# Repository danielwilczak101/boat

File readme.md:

# Project Boat

IMAGE HERE

Welcome to project boat. Check out our [wiki](https://danielwilczak101.github.io/boat/) for more information.

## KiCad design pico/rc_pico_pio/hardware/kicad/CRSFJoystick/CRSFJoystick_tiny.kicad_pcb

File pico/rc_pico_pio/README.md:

#All of the RoboBoat RC Controls code is build on top of the packages below. 

Would like to give them the credit they deserve.
-Dylan

# ELRSJoystick / CRSFJoystick

<https://github.com/mikeneiderhauser/CRSFJoystick>

Named CRSFJoystick as it indicates the wire protocol between the microcontroller (pi pico) and receiver).

Arduino code using the mbed core that runs on a Pi Pico (2040) to emulate a USB HID Joystick

Pirmarily developed to use and ExpressLRS receiver and a HID Joystick for Sim use! It will work with both Tracer and Crossfire as well.

Shout out to CapnBry for the Crsf Library

https://github.com/CapnBry/CRServoF

Shout out to RealRobots.net for the Gamepad Library

https://gitlab.com/realrobots/PicoGamepad/-/tree/master

# Demo Video

- Blank carrier boards for Pi Pico, Tiny 2040, and Waveshare RP2040 (old stock)
- Built and flashed units
- [DIY Section](#diy-hardware)

A few boards that I believe are based off of this project:
- HGLRC Dongle (I have samples from HGLRC on the way)
  - [HGLRC Dongle at HGLRC](https://www.hglrc.com/collections/new-arrivals/products/hglrc-c1-remote-control)
  - [HGLRC C1 Radio Kit with dongle at HGLRC](https://www.hglrc.com/collections/new-arrivals/products/hglrc-c1-remote-control)
  - [HGLRC C1 Radio Kit with dongle at RacedayQuads](https://www.racedayquads.com/products/hglrc-c1-transmitter-elrs-2-4ghz-choose-your-version?keyword=hglrc%20c1)
- Squid Stick (I have personally not tested one)
  -  [Squid Stick at Progressiverc.com](https://www.progressiverc.com/products/squid-stick-elrs-2-4ghz-usb-receiver-module)
  -  Squid Stick at RacedayQuads - Link to be posted when available
- YMZFPV Simulator Adapter (have not yet been able to confirm that this is based off of this project)
  - [YMZFPV Sim Adapter at RacedayQuads](https://www.racedayquads.com/products/ymzfpv-wireless-simulator-adapter-for-sbus-pwm-csfr-choose-your-version?keyword=simulator)

## Compatability

This project was designed primarily with ELRS usage in mind, however this code base has also been tested with TBS Crossfire Receivers (915MHZ) (last tested v6.16) and TBS Tracer Receivers (2.4GHz) (last tested v6.17) and both appear to work! Flight was teseted in the Liftoff simulator.

I no longer have TBS Crossfire nor TBS Tracer TX modules or Receivers so future tests will have to be conducted by others.

### ExpressLRS (Waveshare RP2040)

### Crossfire

### Tracer

# Building / Flashing

I recently converted the projet to PlatformIO to aid in building, board management, etc.  PlatformIO has some known quirks with PiPico boards and I'm going to leave some breadcrumbs here for later.

## VSCode with PlatformIO

### Installing VSCode and PlatformIO
<https://platformio.org/install/ide?install=vscode>

### Build for specific board / environment

At the Bottom of VSCode you will see a tool bar.  Look for `Default (CRSFJoystick)`.  Building in this state will build for all boards / environments defined in the `platformio.ini` file.  To target a sepecific board, Click on `Default (CRSFJoystick)` and select an appropriate option (Note, selection pops up at the top of vscode).

Click on the Checkmark on the bottom toolbar to build for the board / environment you selected.

Click on the `->` on the bottom toolbar to upload to the board.  If upload fails to find your board, please see bothe the [alternative upload](#alternative-upload) section as well as the driver section.

## Alternative upload
This is one of the standard advertised methods for uploading firmware to a pipico based microcontroller board.

Press and hold the bootsel button on your board and either plugin/power on the board or if the board is already powered press and release the reset button.

This will put the board in RP2 Boot mode.

A removable device should pop up or become available on your computer.  Drag and drop the `firmware.u2f` file from the `.pio/build/wavesharerp2040zero/` directory into this device on your computer.  Note replpace wavesharerp2040zero with the environment for your board.

## Drivers
Drivers can be hit or miss for the pipico board and platformio.  

You may need to use zadig to get vscode+platforio to be able to upload directly to the board.
<https://github.com/platformio/platform-raspberrypi/issues/2#issuecomment-828586398>

Below are the drivers I have working on my Windows 11 machine.  You may need to modify the driver selection via zadig and or device manager to get it working.

- Standard Running Mode
  - RaspberryPi Pico (Interface 0)
    - Zadig -> HidUsb v10.0.22621.819
    - Device Manager -> Human Interface Devices -> HID-compliant game controller
  - RaspberryPi Pico (Interface 1)
      - Zadig -> usbser v10.0.22621.1778
      - Device Manager -> Ports (COM & LPT) -> USB Serial Device
- RP2 Boot mode
  - RP2 Boot (Interface 0) 
    - Zadig USBSTOR v10.0.022621.1778 
    - Device Manager -> Disk Drives -> RPI RP2 USB Device 
  - RP2 Boot (Interface 1)
    - Zadig WinUSB v6.1.7600.16385
    Device Manager -> Universal Serial Bus Devices -> RP2 Boot

### Device manager clicks to change driver 
Right Click -> Properties -> Update Driver -> Browse my computer for drivers -> Let me pick from a list of available drivers on my computer

# Flashing ELRS Receiver

Depending on the device you are using, your target may be different.  For all of the DIY version's I've made, I used the HappyModel EP2 Rx.  Other vendors may vary.

## Flashing via Betaflight Passthrough
<https://www.expresslrs.org/software/updating/betaflight-passthrough/>

## Flashing via Wifi
If your receiver is wifi enabled you can also flash it via wifi

<https://www.expresslrs.org/software/updating/wifi-updating/>

# Testing
For a quick test of functionality, I typically go to [GamepadTester](https://hardwaretester.com/gamepad).

Once the Radio is bound to the RX, it should show up in GamePadTester.

# Mappings
This was a quick map and is not fully featured.

On link up/down the onboard Pi Pico LED will light indicating connection

*NOTE* Channel 5, 6, 7, and 8 are mapped both to analog axis as well as joystick buttons.

| Channel     | Logical Mapping  | Joystick Mapping |
| ----------- | ---------------- | ---------------- |
| 1           | A                | X                |
| 2           | E                | Y                |
| 3           | T                | Rx               |
| 4           | R                | Ry               |
| 5           | Channel 5 (Full) AND AUX1 (1510-2011) | Z  AND Button 0 |
| 6           | Channel 6 (Full) AND AUX2 (1510-2011) | Rz AND Button 1 |
| 7           | Channel 7 (Full) AND AUX3 (1510-2011) | S0 AND Button 2 |
| 8           | Channel 8 (Full) AND AUX4 (1510-2001) | S1 AND Button 3 |
| 9           | AUX5 (1510-2011) | Button 4         |
| 10          | AUX6 (1510-2011) | Button 5         |
| 11          | AUX7 (1510-2011) | Button 6         |
| 12          | AUX8 (1510-2011) | Button 7         |
| 13          | Not Used         | Not Used         |
| 14          | Not Used         | Not Used         |
| 15          | LQ - Not Used    | Not Used         |
| 16          | RSSI - Not Used  | Not Used         |

*Note additional button mappings can be created in caliration.h*

# Here below is for DIY Builds and may be slightly outdated
# DIY Hardware

In a nutshell, wire the ELRS RX up to a uart on the pipico, 5v, and gnd.

| Raspberry Pico | ELRS/CRSF Receiver |
| -------------- | ------------------ |
| VBUS (PIN 40)  | 5V                 |
| GND  (PIN 38)  | GND
| GP4  (PIN 6)   | RX                 |
| GP5  (PIN 7)   | TX                 |

Other boards are supported, see the [board_defs.h](./include/board_defs.h) file.

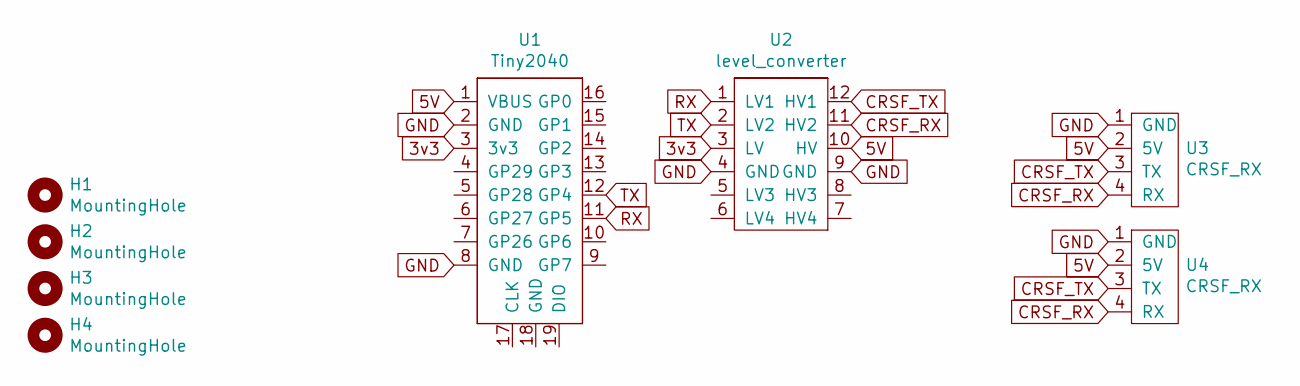
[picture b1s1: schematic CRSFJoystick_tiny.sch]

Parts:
H1, H2, H3, H4: MountingHole; MountingHole_2.2mm_M2
U1: Tiny2040; tiny2040_no_swd
U2: level_converter
U3, U4: CRSF_RX; ELRS_EP2

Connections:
3v3: U1.3 (3v3), U2.3 (LV)
5V: U1.1 (VBUS), U2.10 (HV), U3.2 (5V), U4.2 (5V)
CRSF_RX: U2.11 (HV2), U3.4 (RX), U4.4 (RX)
CRSF_TX: U2.12 (HV1), U3.3 (TX), U4.3 (TX)
GND: U1.2 (GND), U1.8 (GND), U2.4 (GND), U2.9 (GND), U3.1 (GND), U4.1 (GND)
RX: U1.11 (GP5), U2.1 (LV1)
TX: U1.12 (GP4), U2.2 (LV2)

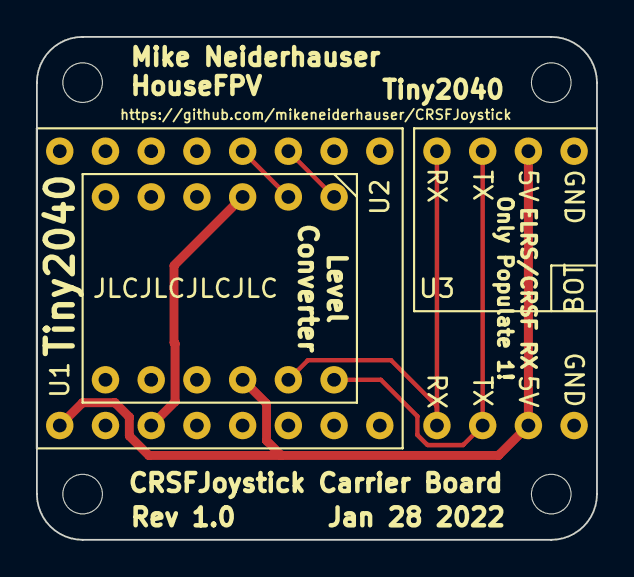
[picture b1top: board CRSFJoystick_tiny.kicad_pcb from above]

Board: 2 copper layers, 31.1 x 27.9 mm, 8 parts (1 on the bottom side), 7 nets.

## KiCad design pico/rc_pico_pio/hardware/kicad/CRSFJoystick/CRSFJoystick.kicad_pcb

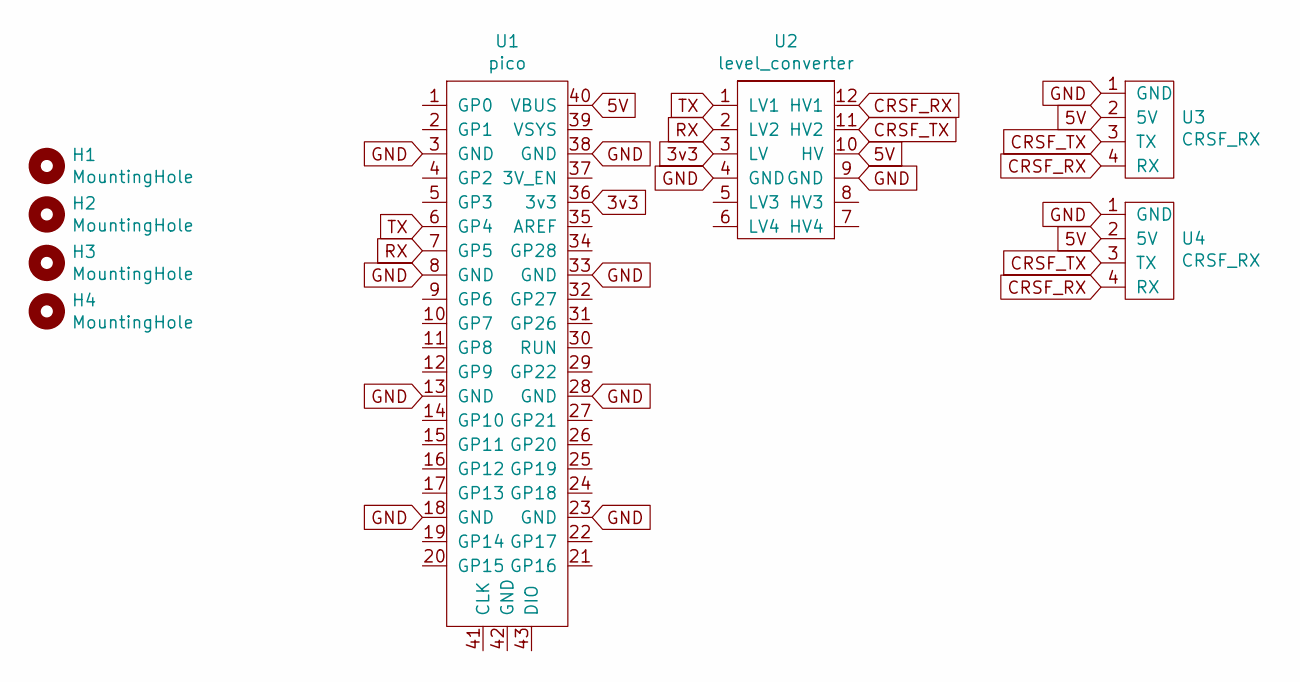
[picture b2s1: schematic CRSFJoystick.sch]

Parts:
H1, H2, H3, H4: MountingHole; MountingHole_2.2mm_M2
U1: pico; pico_no_swd
U2: level_converter
U3, U4: CRSF_RX; ELRS_EP2

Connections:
3v3: U1.36 (3v3), U2.3 (LV)
5V: U1.40 (VBUS), U2.10 (HV), U3.2 (5V), U4.2 (5V)
CRSF_RX: U2.12 (HV1), U3.4 (RX), U4.4 (RX)
CRSF_TX: U2.11 (HV2), U3.3 (TX), U4.3 (TX)
GND: U1.3 (GND), U1.8 (GND), U1.13 (GND), U1.18 (GND), U1.23 (GND), U1.28 (GND), U1.33 (GND), U1.38 (GND), U2.4 (GND), U2.9 (GND), U3.1 (GND), U4.1 (GND)
RX: U1.7 (GP5), U2.2 (LV2)
TX: U1.6 (GP4), U2.1 (LV1)

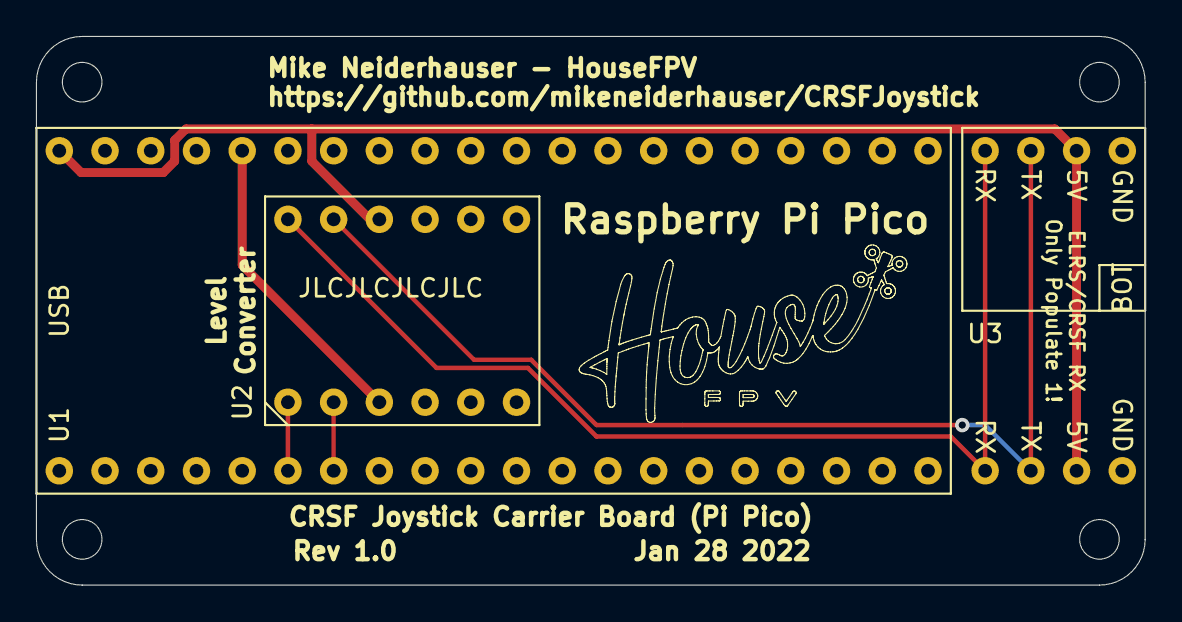
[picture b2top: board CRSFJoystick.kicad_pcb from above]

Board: 2 copper layers, 61.6 x 30.5 mm, 8 parts (1 on the bottom side), 7 nets.

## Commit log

2024-01-28 init
2024-01-28 Updated.
2024-01-28 Updated plugin.
2024-01-29 upload working V1 rc and autonomous pico code
2024-01-29 Updated docs.
2024-01-30 update rc pico PIO code
2024-01-30 update pio rc code
2024-01-30 rc code upload lib
2024-01-31 Updated training
2024-01-31 Added servo offset to get both motors to point striaght in rc pico code
2024-01-31 Update.
2024-01-31 added auto pico code to recieve throttle and servo values via serial
2024-01-31 update auto pico to take in throttle via serial.
2024-01-31 update auto pico to take in servo angle via serial
2024-02-03 Deployed 1bd9858 with MkDocs version: 1.5.3
2024-02-24 Last Working Code from Proto PCBS. Moving Forward will be testing with new PCB v0.1 from 2/3/24
2024-02-25 reconfigured RC Pico code for new Autonomous Boat V0.1 PCB
2024-03-03 update rc to autonomous switch
2024-03-06 add watercannon code
2024-03-21 update code from mac
2024-03-21 update code with comments
2024-03-21 fixed merge
